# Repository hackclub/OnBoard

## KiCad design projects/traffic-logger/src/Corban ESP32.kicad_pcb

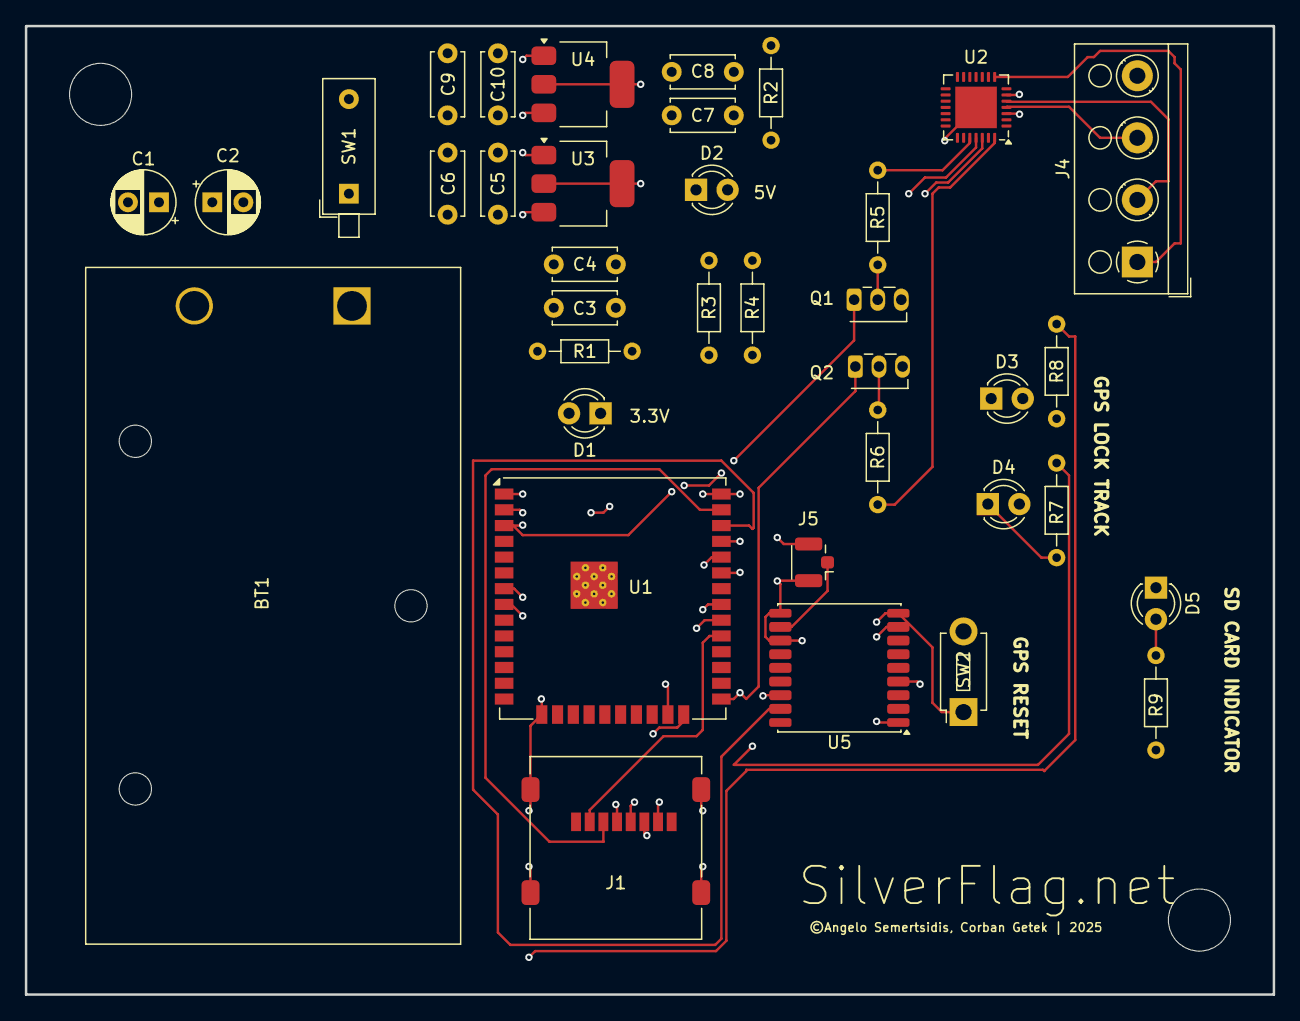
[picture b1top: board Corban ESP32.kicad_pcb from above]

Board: 4 copper layers, 100.5 x 78.0 mm, 37 parts (0 on the bottom side), 24 nets.

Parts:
BT1: 9v; BatteryHolder_Eagle_12BH611-GR
C1, C2: 100µF; CP_Radial_D5.0mm_P2.50mm
C3, C5, C7, C9: 0.1µF; C_Disc_D5.0mm_W2.5mm_P5.00mm
C4, C8: 10µF; C_Disc_D5.0mm_W2.5mm_P5.00mm
C6, C10: 0.22µF; C_Disc_D5.0mm_W2.5mm_P5.00mm
D1, D2, D5: LED; LED_D3.0mm
D3, D4: LED_D3.0mm
J1: Micro_SD_Card; microSD_HC_Molex_47219-2001
J4: TerminalBlock_RND_205-00003_1x04_P5.00mm_Horizont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; TerminalBlock_RND_205-00003_1x04_P5.00mm_Horizontal
J5: GPS Antenna; U.FL_Hirose_U.FL-R-SMT-1_Vertical
Q1, Q2: NPN; ONSemi_QSE15x
R1, R2: 1kΩ; R_Axial_DIN0204_L3.6mm_D1.6mm_P7.62mm_Horizontal
R3, R4: 10KΩ; R_Axial_DIN0204_L3.6mm_D1.6mm_P7.62mm_Horizontal
R5, R6: 100Ω; R_Axial_DIN0204_L3.6mm_D1.6mm_P7.62mm_Horizontal
R7, R8, R9: R_Axial_DIN0204_L3.6mm_D1.6mm_P7.62mm_Horizontal
SW1: SW_DIP_SPSTx01_Piano_10.8x4.1mm_W7.62mm_P2.54mm
SW2: SW_PUSH_1P1T_6x3.5mm_H5.0_APEM_MJTP1250
U1: ESP32-WROOM-32UE
U2: CP2102N-Axx-xQFN28; QFN-28-1EP_5x5mm_P0.5mm_EP3.35x3.35mm
U3: AMS1117-3.3; SOT-223-3_TabPin2
U4: AMS1117-5; SOT-223-3_TabPin2
U5: MAX-M10S; ublox_MAX

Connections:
+3.3V: C3.2, C4.1, D1.1 (K), J1.4 (VDD), R1.1, R1.2, R3.2, R4.2, SW2.1, U1.2 (VDD), U3.2 (VO), U5.8 (VCC), U5.9 (~RESET)
+5V: C7.2, C8.1, D2.1 (K), R2.1, R2.2, U2.6 (VDD), U4.2 (VO)
D+: J4.3, U2.4 (D+)
D-: J4.2, U2.5 (D-)
DTR: R6.1, U2.28 (~DTR)
EN: Q1.1 (C), R3.1, U1.3 (EN)
GND: BT1.2 (-), C1.2, C2.2, C3.1, C4.2, C5.1, C6.1, C7.1, C8.2, C9.1, C10.1, D1.2 (A), D2.2 (A), D3.2, D4.2, J1.6 (VSS), J1.9 (SHIELD), J4.4, J5.2 (Ext), Q1.3 (E), Q2.3 (E), R9.2, SW1.2, SW2.2, U1.1 (GND), U1.15 (GND), U1.38 (GND), U1.39 (GND), U2.3 (GND), U2.29 (GND), U3.1 (GND), U4.1 (GND), U5.1 (GND), U5.10 (GND), U5.12 (GND)
IO1: Q2.1 (C), R4.1, U1.25 (IO0)
IO5: J1.2 (DAT3/CD), U1.29 (IO5)
IO18: J1.5 (CLK), U1.30 (IO18)
IO19: J1.7 (DAT0), U1.31 (IO19)
IO21: U1.33 (IO21), U5.16 (SDA)
IO22: U1.36 (IO22), U5.17 (SCL)
IO23: J1.3 (CMD), U1.37 (IO23)
unnamed: BT1.1 (+), C1.1, C2.1
unnamed: J5.1 (In), U5.11 (RF_IN)
unnamed: Q1.2 (B), R5.2
unnamed: Q2.2 (B), R6.2
unnamed: C5.2, C6.2, SW1.1, U3.3 (VI)
unnamed: C9.2, C10.2, U4.3 (VI)
RTS: R5.1, U2.24 (~RTS)
TRANS-1: U1.35 (TXD0/IO1), U2.25 (RXD)
TRANS-2: U1.24 (IO2), U2.26 (TXD)
VBUS: J4.1, U2.8 (VBUS)

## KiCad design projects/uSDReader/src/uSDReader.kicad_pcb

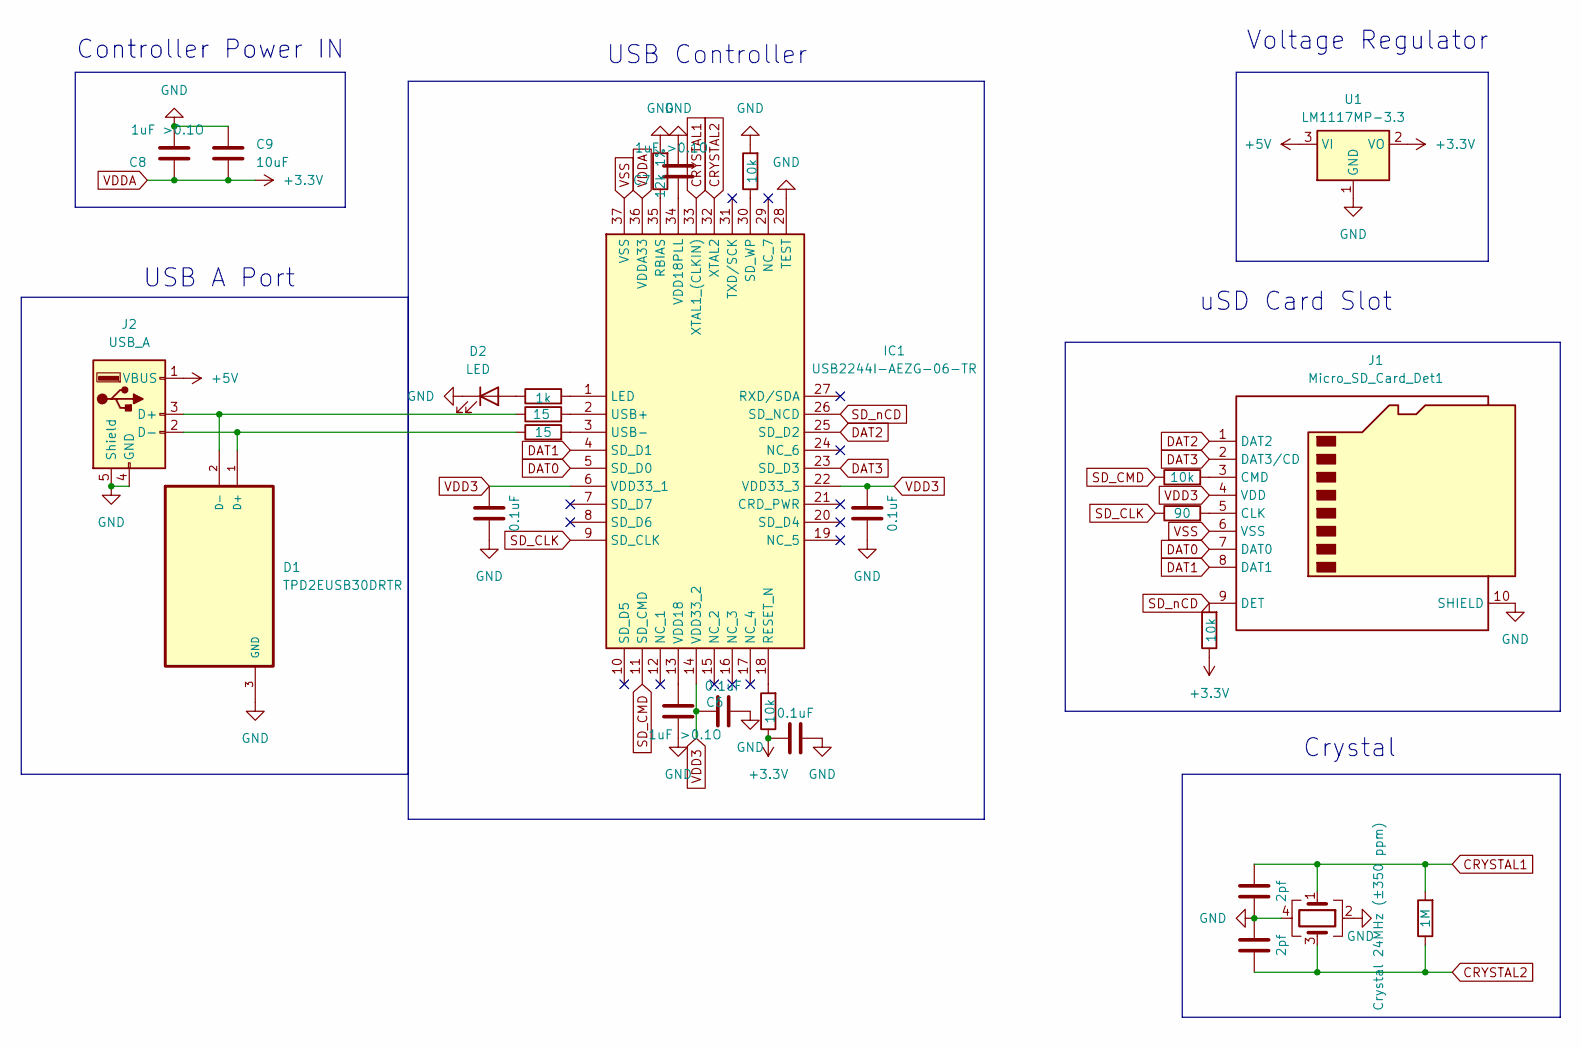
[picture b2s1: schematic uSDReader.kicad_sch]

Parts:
C3, C4, C5, C10: 0.1uF; C_0402_1005Metric
C6, C7, C8: 1uF >0.1O; C_0402_1005Metric
C9: 10uF; C_0402_1005Metric
C11, C12: 2pf; C_0402_1005Metric
D1: TPD2EUSB30DRTR; SOTFL35P100X50-3N
D2: LED; LED_0805_2012Metric
IC1: USB2244I-AEZG-06-TR; QFN50P600X600X90-37N-D; Mouser Part Number 579-USB2244IAEZG06TR
J1: Micro_SD_Card_Det1; TF-015
J2: USB_A; USB_A_Receptacle_GCT_USB1046
R1: 1M; R_0603_1608Metric
R2: 90; R_0402_1005Metric
R3, R8, R9, R10: 10k; R_0402_1005Metric
R4, R5: 15; R_0402_1005Metric
R6: 12k 1%; R_0402_1005Metric
R7: 1k; R_0402_1005Metric
U1: LM1117MP-3.3; SOT-223-3_TabPin2
Y2: Crystal 24MHz (±350 ppm); Crystal_SMD_2016-4Pin_2.0x1.6mm

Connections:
+5V: J2.1 (VBUS), U1.3 (VI)
CRYSTAL1: C12.2, IC1.33 (XTAL1_(CLKIN)), R1.2, Y2.1
CRYSTAL2: C11.1, IC1.32 (XTAL2), R1.1, Y2.3
DAT0: IC1.5 (SD_D0), J1.7 (DAT0)
DAT1: IC1.4 (SD_D1), J1.8 (DAT1)
DAT2: IC1.25 (SD_D2), J1.1 (DAT2)
DAT3: IC1.23 (SD_D3), J1.2 (DAT3/CD)
GND: C3.1, C4.2, C5.2, C6.2, C7.2, C8.2, C9.1, C10.2, C11.2, C12.1, D1.3 (GND), D2.1 (K), IC1.28 (TEST), J1.10 (SHIELD), J2.4 (GND), J2.5 (Shield), R6.2, R9.2, U1.1 (GND), Y2.2, Y2.4
unnamed: D1.1 (D+), J2.2 (D-), R5.1
unnamed: D1.2 (D-), J2.3 (D+), R4.1
unnamed: D2.2 (A), R7.1
unnamed: IC1.1 (LED), R7.2
unnamed: IC1.35 (RBIAS), R6.1
unnamed: IC1.18 (RESET_N), R8.2
unnamed: IC1.30 (SD_WP), R9.1
unnamed: IC1.2 (USB+), R4.2
unnamed: IC1.3 (USB-), R5.2
unnamed: C6.1, IC1.13 (VDD18)
unnamed: C7.1, IC1.34 (VDD18PLL)
unnamed: J1.5 (CLK), R2.2
unnamed: J1.3 (CMD), R3.2
SD_CLK: IC1.9 (SD_CLK), R2.1
SD_CMD: IC1.11 (SD_CMD), R3.1
SD_nCD: IC1.26 (SD_NCD), J1.9 (DET), R10.2
VDD3: C3.2, C4.1, C5.1, IC1.6 (VDD33_1), IC1.14 (VDD33_2), IC1.22 (VDD33_3), J1.4 (VDD)
VDDA: C8.1, C9.2, C10.1, IC1.36 (VDDA33), R8.1, R10.1, U1.2 (VO)
VSS: IC1.37 (VSS), J1.6 (VSS)

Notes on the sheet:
uSD Card Slot
Voltage Regulator
Crystal
USB Controller
USB A Port
Controller Power IN

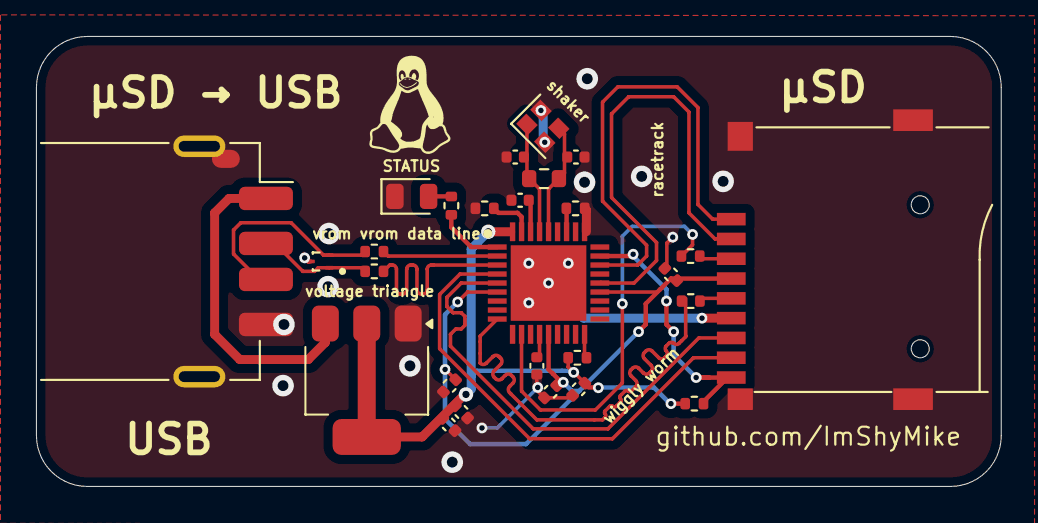
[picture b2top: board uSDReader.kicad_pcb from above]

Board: 2 copper layers, 53.6 x 25.0 mm, 27 parts (0 on the bottom side), 27 nets.

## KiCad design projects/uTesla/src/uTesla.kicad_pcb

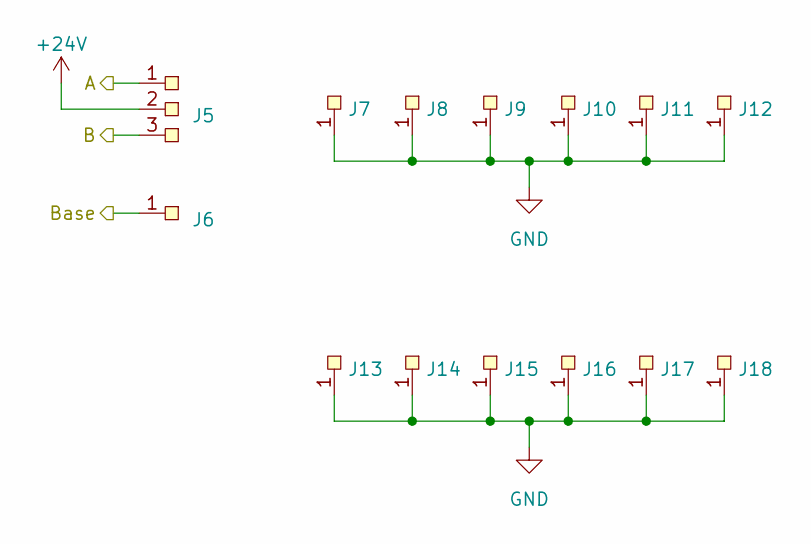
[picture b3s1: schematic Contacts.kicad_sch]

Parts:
J5: SolderPad-3pin
J6, J7, J8, J9, J10, J11, J12, J13, J14, J15, J16, J17, J18: SolderPad-1pin

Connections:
+24V: J5.2; also elsewhere on the board
/Contacts/A: J5.1; also elsewhere on the board
/Contacts/B: J5.3; also elsewhere on the board
/Contacts/Base: J6.1; also elsewhere on the board
GND: J7.1, J8.1, J9.1, J10.1, J11.1, J12.1, J13.1, J14.1, J15.1, J16.1, J17.1, J18.1; also elsewhere on the board

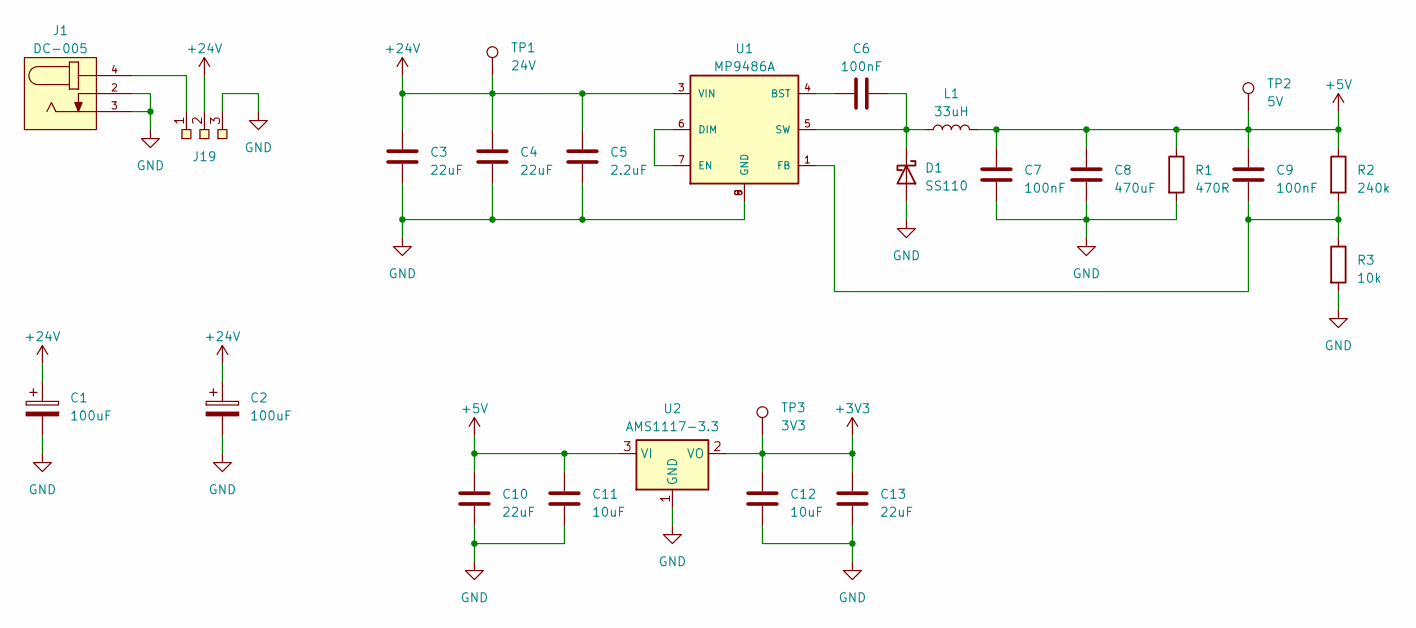
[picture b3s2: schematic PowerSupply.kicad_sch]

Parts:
C1, C2: 100uF; CP_Radial_D8.0mm_P3.80mm
C3, C4, C10, C13: 22uF; C_0603_1608Metric
C5: 2.2uF; C_0603_1608Metric
C6, C7, C9: 100nF; C_0603_1608Metric
C8: 470uF; C_0603_1608Metric
C11, C12: 10uF; C_0603_1608Metric
D1: SS110; D_SMA
J1: DC-005; NINIGI_DC-005
J19: SolderPad-3pin
L1: 33uH; L_Toroid_Vertical_L26.7mm_W14.0mm_P10.16mm_Pulse_D
R1: 470R; R_0603_1608Metric
R2: 240k; R_0603_1608Metric
R3: 10k; R_0603_1608Metric
TP1: 24V; TestPoint_Pad_D2.0mm
TP2: 5V; TestPoint_Pad_D2.0mm
TP3: 3V3; TestPoint_Pad_D2.0mm
U1: MP9486A; SOIC-8EP
U2: AMS1117-3.3; SOT-223-3_TabPin2

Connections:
+3V3: C12.1, C13.1, TP3.1, U2.2 (VO); also elsewhere on the board
+5V: C7.1, C8.1, C9.1, C10.1, C11.1, L1.2, R1.1, R2.1, TP2.1, U2.3 (VI); also elsewhere on the board
+24V: C1.1, C2.1, C3.1, C4.1, C5.1, J19.2, TP1.1, U1.3 (VIN); also elsewhere on the board
GND: C1.2, C2.2, C3.2, C4.2, C5.2, C7.2, C8.2, C10.2, C11.2, C12.2, C13.2, D1.2 (A), J1.2, J1.3, J19.3, R1.2, R3.2, U1.8 (GND), U1.9 (GND), U2.1 (GND); also elsewhere on the board
unnamed: C6.2, D1.1 (K), L1.1, U1.5 (SW)
unnamed: J1.4, J19.1
unnamed: C6.1, U1.4 (BST)
unnamed: U1.6 (DIM), U1.7 (EN)
unnamed: C9.2, R2.2, R3.1, U1.1 (FB)

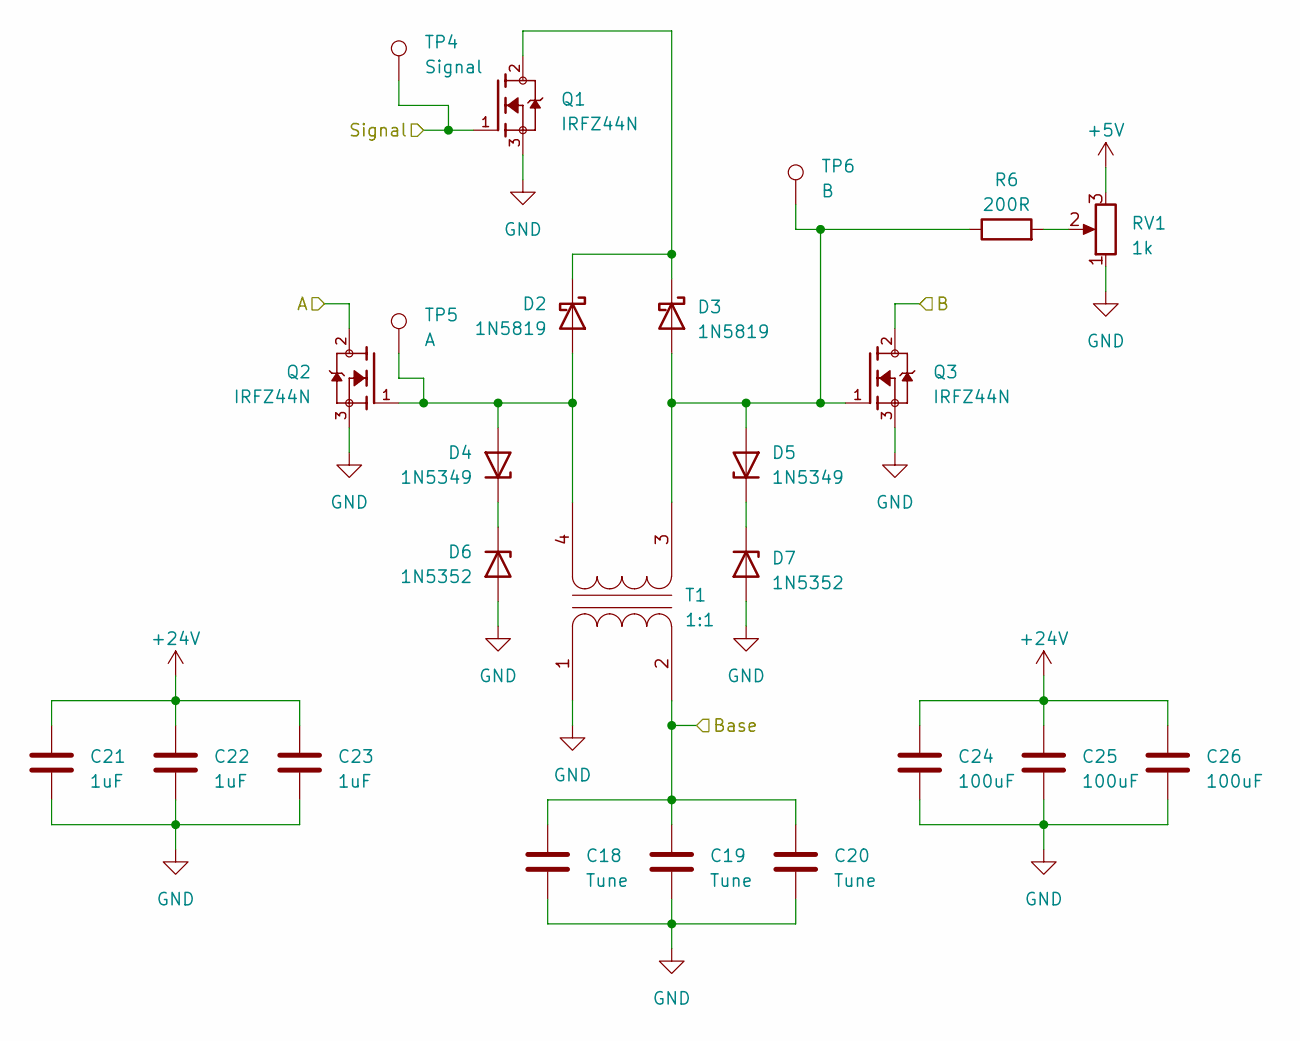
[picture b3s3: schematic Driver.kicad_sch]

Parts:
C18, C19, C20: Tune; C_0603_1608Metric
C21, C22, C23: 1uF; C_0603_1608Metric
C24, C25, C26: 100uF; CP_Radial_D8.0mm_P3.80mm
D2, D3: 1N5819; D_DO-41_SOD81_P10.16mm_Horizontal
D4, D5: 1N5349; D_DO-41_SOD81_P10.16mm_Horizontal
D6, D7: 1N5352; D_DO-41_SOD81_P10.16mm_Horizontal
Q1, Q2, Q3: IRFZ44N; TO254P1016X419X2286-3; PARTREV 09/21/10
R6: 200R; R_0603_1608Metric
RV1: 1k; Potentiometer_Runtron_RM-065_Vertical
T1: 1:1; Transformer_Toroid_Horizontal_D9.0mm_Amidon-T30
TP4: Signal; TestPoint_Pad_D2.0mm
TP5: A; TestPoint_Pad_D2.0mm
TP6: B; TestPoint_Pad_D2.0mm

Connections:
+5V: RV1.3; also elsewhere on the board
+24V: C21.1, C22.1, C23.1, C24.1, C25.1, C26.1; also elsewhere on the board
/Contacts/A: Q2.2; also elsewhere on the board
/Contacts/B: Q3.2; also elsewhere on the board
/Contacts/Base: C18.1, C19.1, C20.1, T1.2 (AB); also elsewhere on the board
/Driver/Signal: Q1.1, TP4.1; also elsewhere on the board
GND: C18.2, C19.2, C20.2, C21.2, C22.2, C23.2, C24.2, C25.2, C26.2, D6.2 (A), D7.2 (A), Q1.3, Q2.3, Q3.3, RV1.1, T1.1 (AA); also elsewhere on the board
unnamed: D2.2 (A), D4.2 (A), Q2.1, T1.4 (SB), TP5.1
unnamed: D2.1 (K), D3.1 (K), Q1.2
unnamed: D3.2 (A), D5.2 (A), Q3.1, R6.1, T1.3 (SA), TP6.1
unnamed: D4.1 (K), D6.1 (K)
unnamed: D5.1 (K), D7.1 (K)
unnamed: R6.2, RV1.2

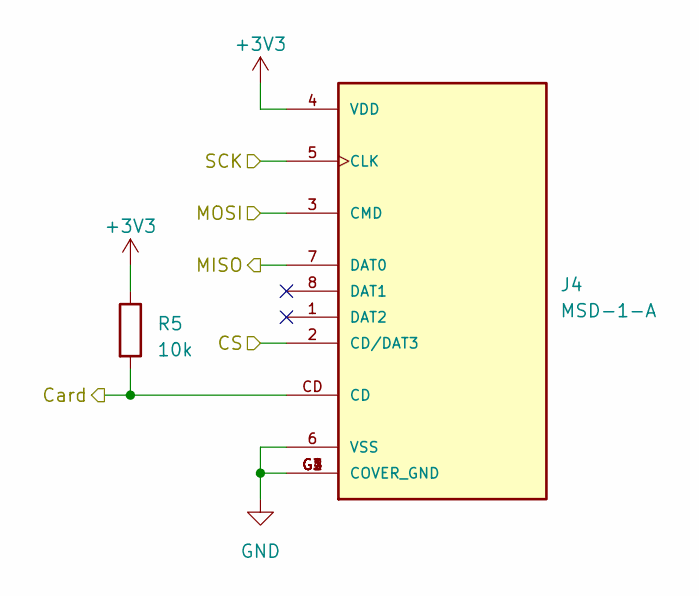
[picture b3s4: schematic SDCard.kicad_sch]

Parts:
J4: MSD-1-A; CUI_MSD-1-A; PARTREV 1.0
R5: 10k; R_0603_1608Metric

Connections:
+3V3: J4.4 (VDD), R5.1; also elsewhere on the board
/Microcontroller/CS: J4.2 (CD/DAT3); also elsewhere on the board
/Microcontroller/Card: J4.CD, R5.2; also elsewhere on the board
/Microcontroller/MISO: J4.7 (DAT0); also elsewhere on the board
/Microcontroller/MOSI: J4.3 (CMD); also elsewhere on the board
/Microcontroller/SCK: J4.5 (CLK); also elsewhere on the board
GND: J4.6 (VSS), J4.G1 (COVER_GND), J4.G2 (COVER_GND), J4.G3 (COVER_GND), J4.G4 (COVER_GND); also elsewhere on the board

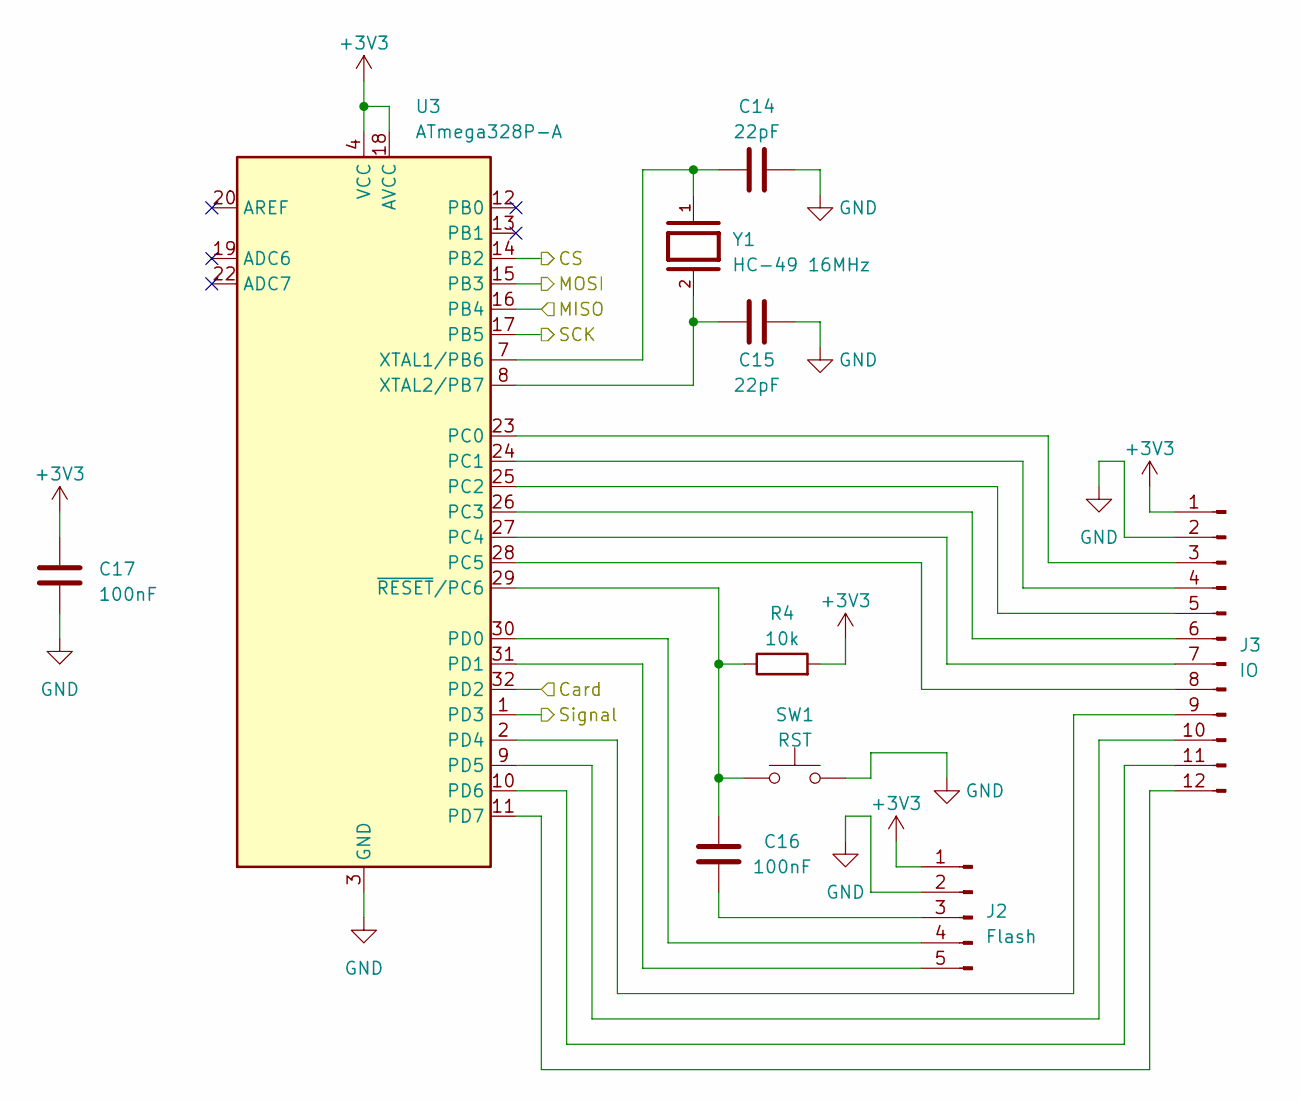
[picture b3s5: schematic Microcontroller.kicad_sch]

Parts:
C14, C15: 22pF; C_0603_1608Metric
C16, C17: 100nF; C_0603_1608Metric
J2: Flash; PinHeader_1x05_P2.54mm_Vertical
J3: IO; PinHeader_1x12_P2.54mm_Vertical
R4: 10k; R_0603_1608Metric
SW1: RST; SW_PUSH_6mm
U3: ATmega328P-A; TQFP-32_7x7mm_P0.8mm
Y1: HC-49 16MHz; XTAL_HC49P488W43L1150T466H350; PARTREV 1.0

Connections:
+3V3: C17.1, J2.1, J3.1, R4.2, U3.4 (VCC), U3.6 (VCC), U3.18 (AVCC); also elsewhere on the board
/Driver/Signal: U3.1 (PD3); also elsewhere on the board
/Microcontroller/CS: U3.14 (PB2); also elsewhere on the board
/Microcontroller/Card: U3.32 (PD2); also elsewhere on the board
/Microcontroller/MISO: U3.16 (PB4); also elsewhere on the board
/Microcontroller/MOSI: U3.15 (PB3); also elsewhere on the board
/Microcontroller/SCK: U3.17 (PB5); also elsewhere on the board
GND: C14.2, C15.2, C17.2, J2.2, J3.2, SW1.2, U3.3 (GND), U3.5 (GND), U3.21 (GND); also elsewhere on the board
unnamed: C16.1, J2.3
unnamed: J2.4, U3.30 (PD0)
unnamed: J2.5, U3.31 (PD1)
unnamed: J3.3, U3.23 (PC0)
unnamed: J3.4, U3.24 (PC1)
unnamed: J3.5, U3.25 (PC2)
unnamed: J3.6, U3.26 (PC3)
unnamed: J3.7, U3.27 (PC4)
unnamed: J3.8, U3.28 (PC5)
unnamed: J3.9, U3.2 (PD4)
unnamed: J3.10, U3.9 (PD5)
unnamed: J3.11, U3.10 (PD6)
unnamed: J3.12, U3.11 (PD7)
unnamed: C14.1, U3.7 (XTAL1/PB6), Y1.1
unnamed: C15.1, U3.8 (XTAL2/PB7), Y1.2
unnamed: C16.2, R4.1, SW1.1, U3.29 (~RESET/PC6)

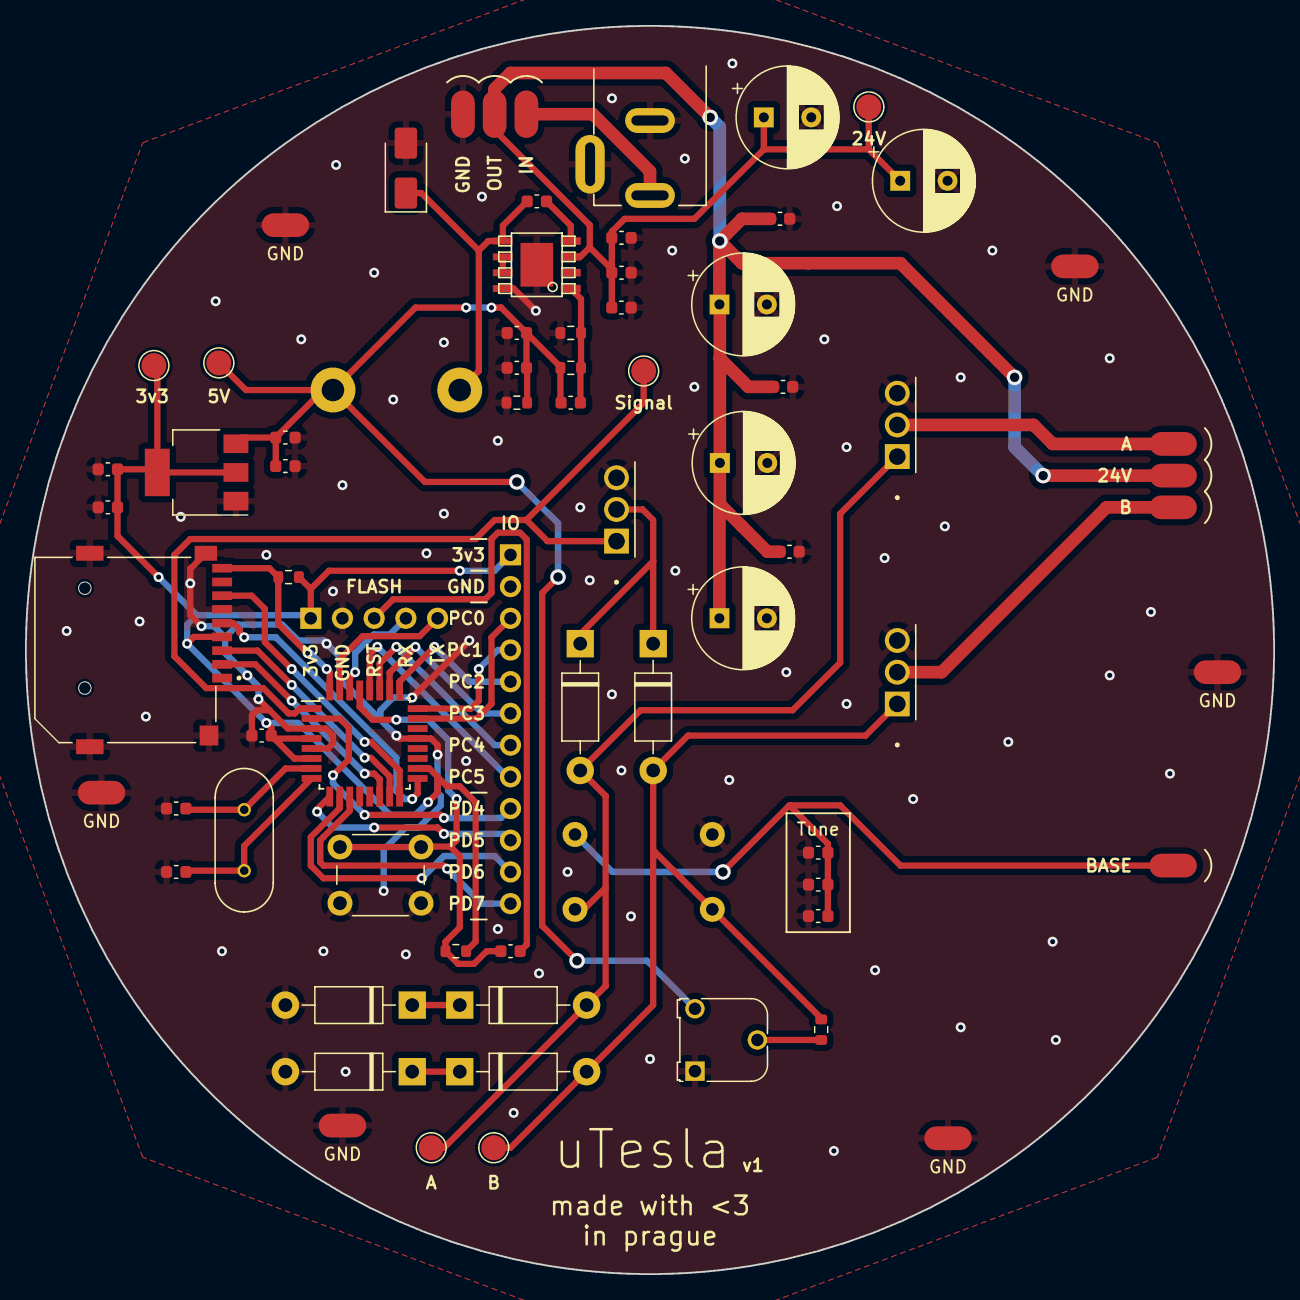
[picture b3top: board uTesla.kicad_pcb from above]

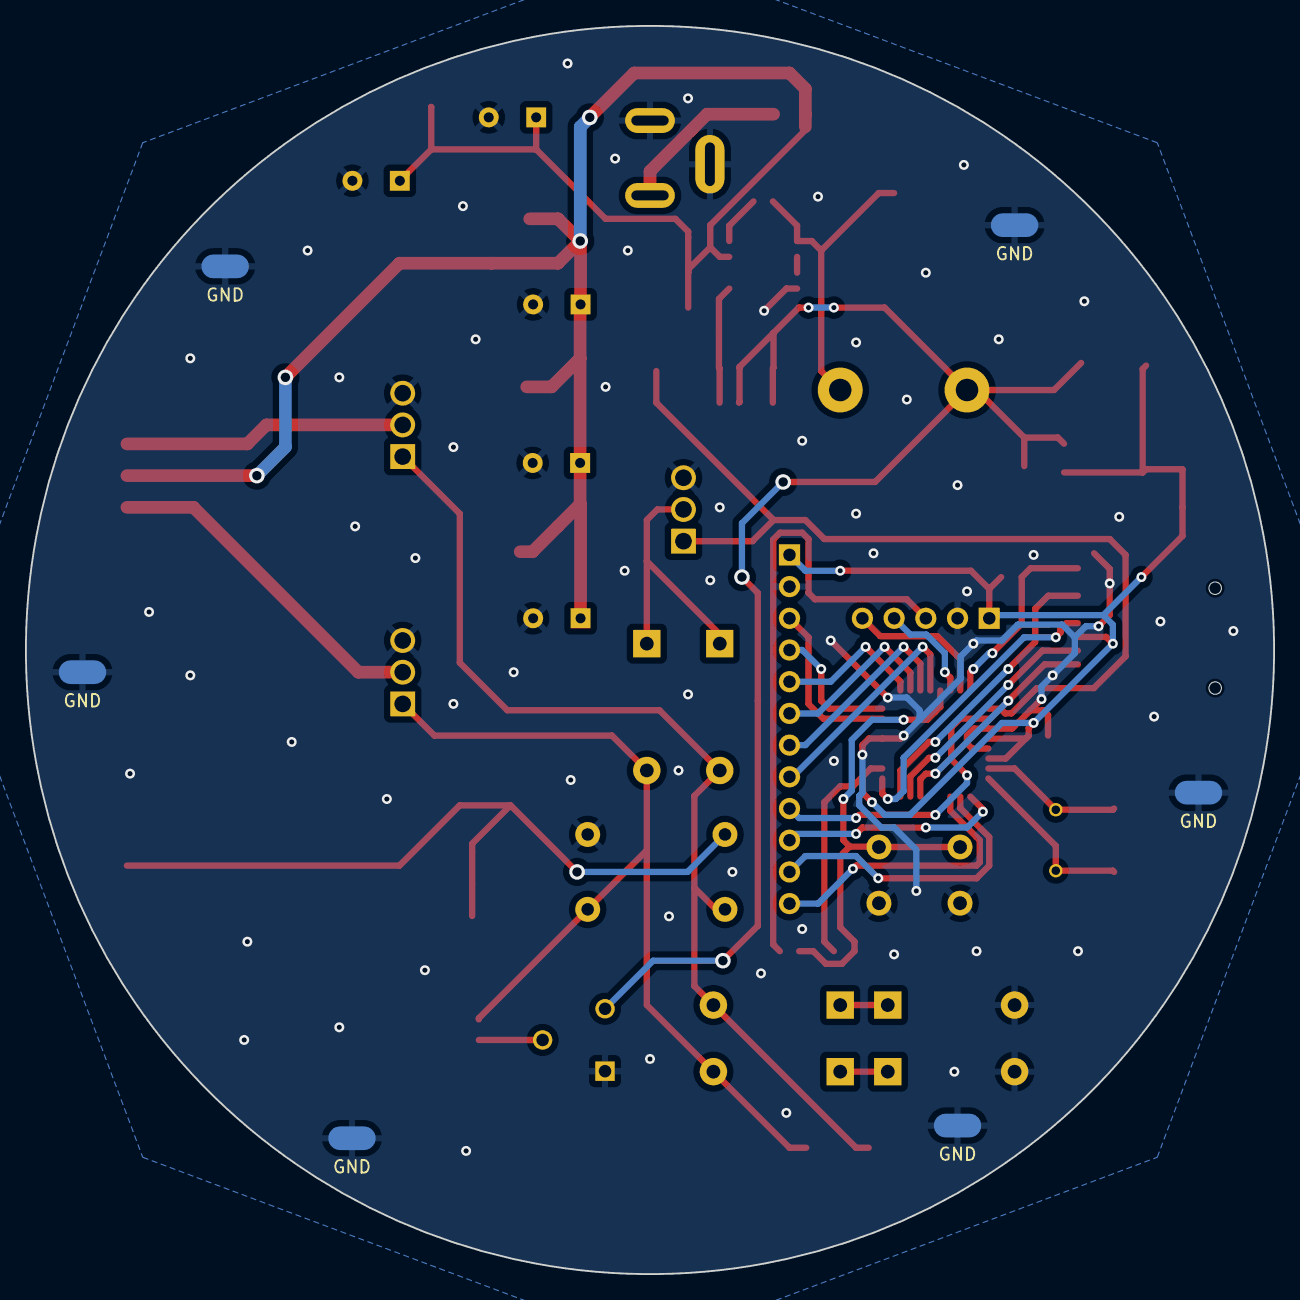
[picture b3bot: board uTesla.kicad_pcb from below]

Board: 2 copper layers, 100.0 x 100.0 mm, 75 parts (6 on the bottom side), 40 nets.

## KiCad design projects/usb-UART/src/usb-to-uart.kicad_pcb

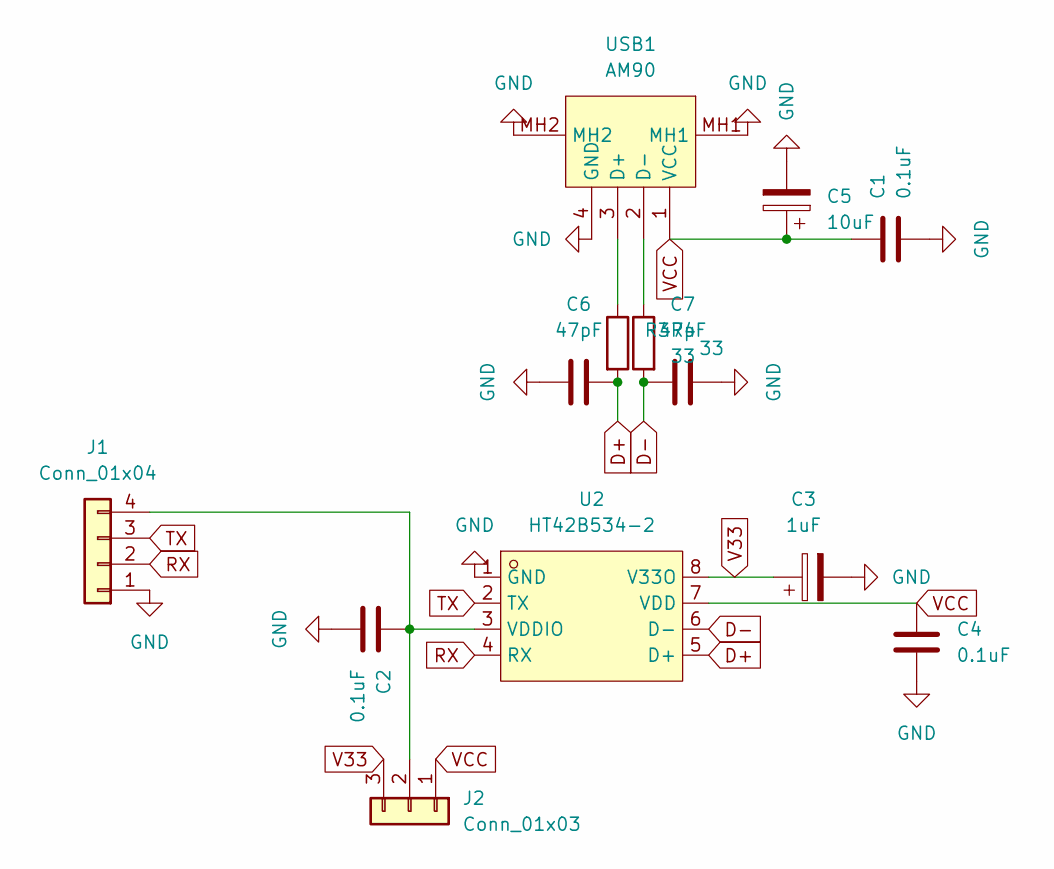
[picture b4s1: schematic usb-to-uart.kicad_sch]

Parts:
C1, C2, C4: 0.1uF; C_0603_1608Metric
C3: 1uF; CP_Elec_4x5.4; LCSC C4747972
C5: 10uF; C_Elec_5x5.4
C6, C7: 47pF; C_0603_1608Metric
J1: Conn_01x04; PinHeader_1x04_P2.54mm_Horizontal
J2: Conn_01x03; PinHeader_1x03_P2.54mm_Vertical
R3, R4: 33; R_0603_1608Metric
U2: HT42B534-2; SOP-8_L4.9-W3.9-P1.27-LS6.0-BL; LCSC Part C493294
USB1: AM90; USB-AM-TH_AM90; LCSC Part C404965

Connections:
D+: C6.1, R3.2, U2.5 (D+)
D-: C7.1, R4.2, U2.6 (D-)
GND: C1.2, C2.2, C3.2, C4.2, C5.2, C6.2, C7.2, J1.1, U2.1 (GND), USB1.4 (GND), USB1.MH1, USB1.MH2
unnamed: C2.1, J1.4, J2.2, U2.3 (VDDIO)
unnamed: R3.1, USB1.3 (D+)
unnamed: R4.1, USB1.2 (D-)
RX: J1.2, U2.4 (RX)
TX: J1.3, U2.2 (TX)
V33: C3.1, J2.3, U2.8 (V33O)
VCC: C1.1, C4.1, C5.1, J2.1, U2.7 (VDD), USB1.1 (VCC)

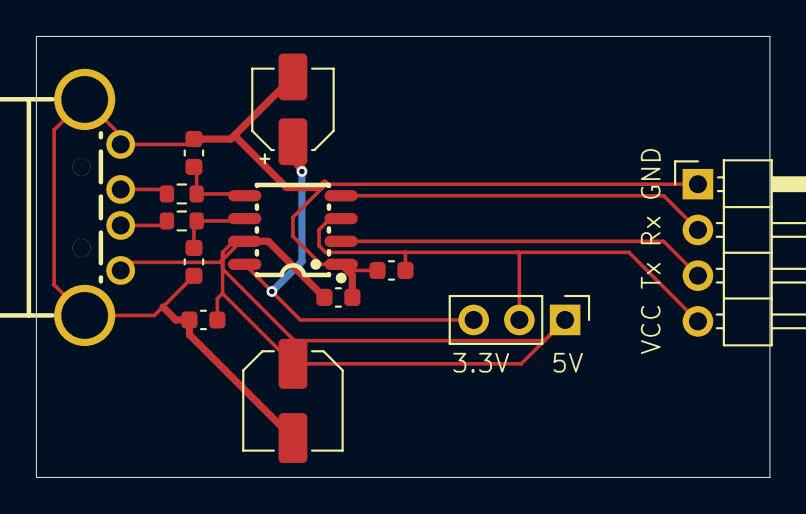
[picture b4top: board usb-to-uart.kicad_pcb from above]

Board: 2 copper layers, 40.8 x 24.5 mm, 13 parts (0 on the bottom side), 10 nets.

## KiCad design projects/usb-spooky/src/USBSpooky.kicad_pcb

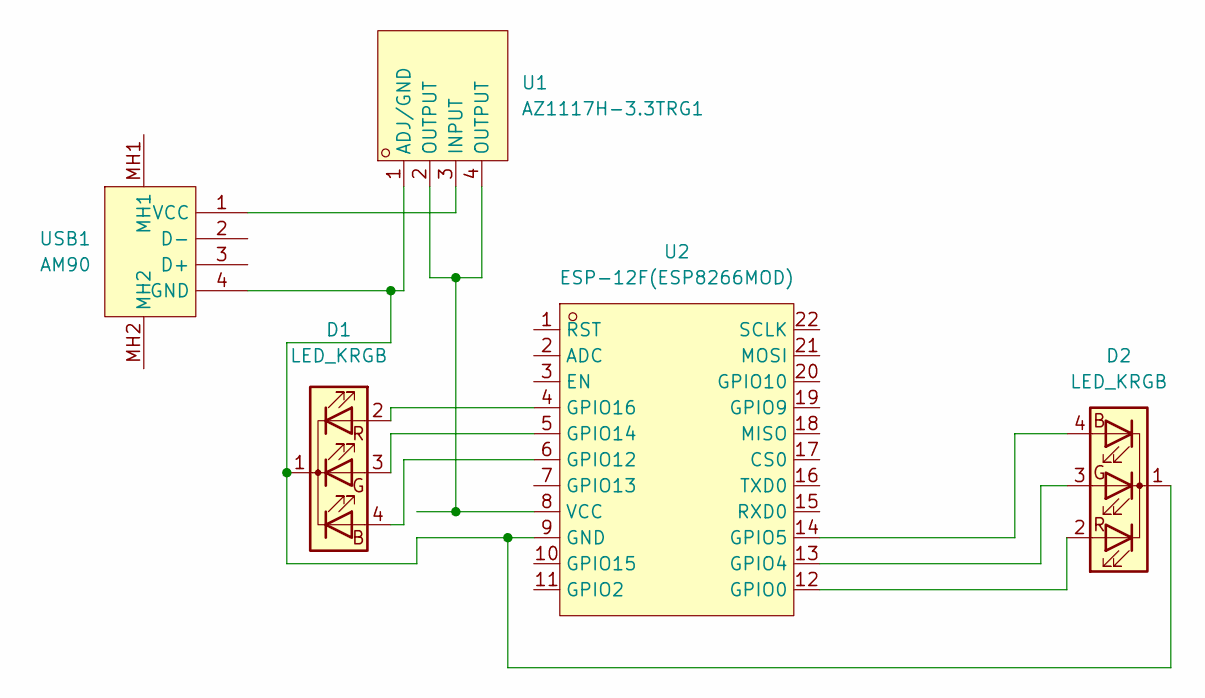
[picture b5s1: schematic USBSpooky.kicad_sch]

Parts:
D1, D2: LED_KRGB; LED_RGB_1210
U1: AZ1117H-3.3TRG1; SOT-223-3_L6.5-W3.4-P2.30-LS7.0-BR; LCSC Part C110474
U2: ESP-12F(ESP8266MOD); WIFIM-SMD_ESP-12F-ESP8266MOD; LCSC Part C82891
USB1: AM90; USB-AM-TH_AM90; LCSC Part C404965

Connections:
unnamed: D1.4 (BA), U2.6 (GPIO12)
unnamed: D1.3 (GA), U2.5 (GPIO14)
unnamed: D1.1 (K), D2.1 (K), U1.1 (ADJ/GND), U2.9 (GND), USB1.4 (GND)
unnamed: D1.2 (RA), U2.4 (GPIO16)
unnamed: D2.4 (BA), U2.14 (GPIO5)
unnamed: D2.3 (GA), U2.13 (GPIO4)
unnamed: D2.2 (RA), U2.12 (GPIO0)
unnamed: U1.3 (INPUT), USB1.1 (VCC)
unnamed: U1.2 (OUTPUT), U1.4 (OUTPUT), U2.8 (VCC)

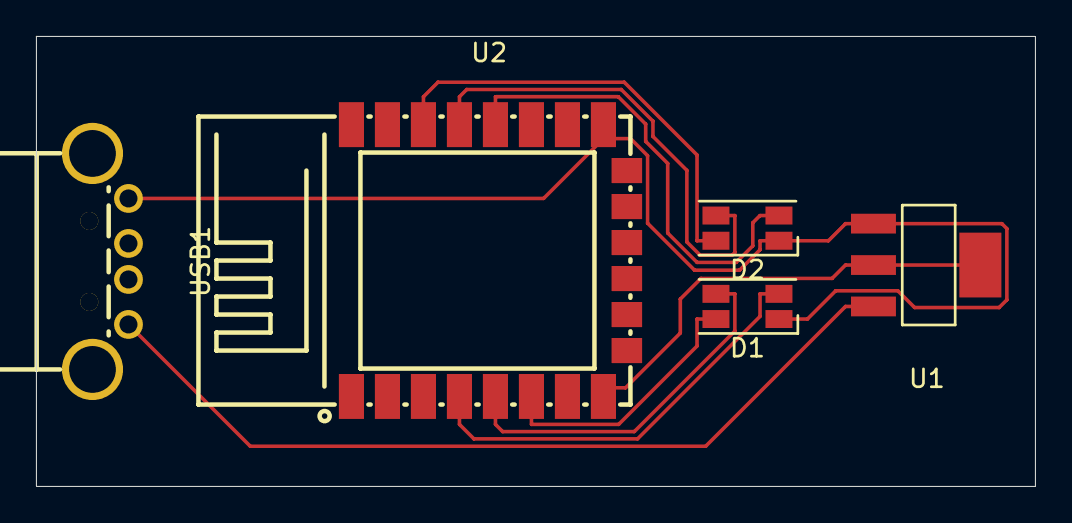
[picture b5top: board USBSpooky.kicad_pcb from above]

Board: 2 copper layers, 55.5 x 25.0 mm, 5 parts (0 on the bottom side), 9 nets.

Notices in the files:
projects/traffic-logger/src/Corban ESP32.kicad_pcb:
©Angelo Semertsidis, Corban Getek | 2025
